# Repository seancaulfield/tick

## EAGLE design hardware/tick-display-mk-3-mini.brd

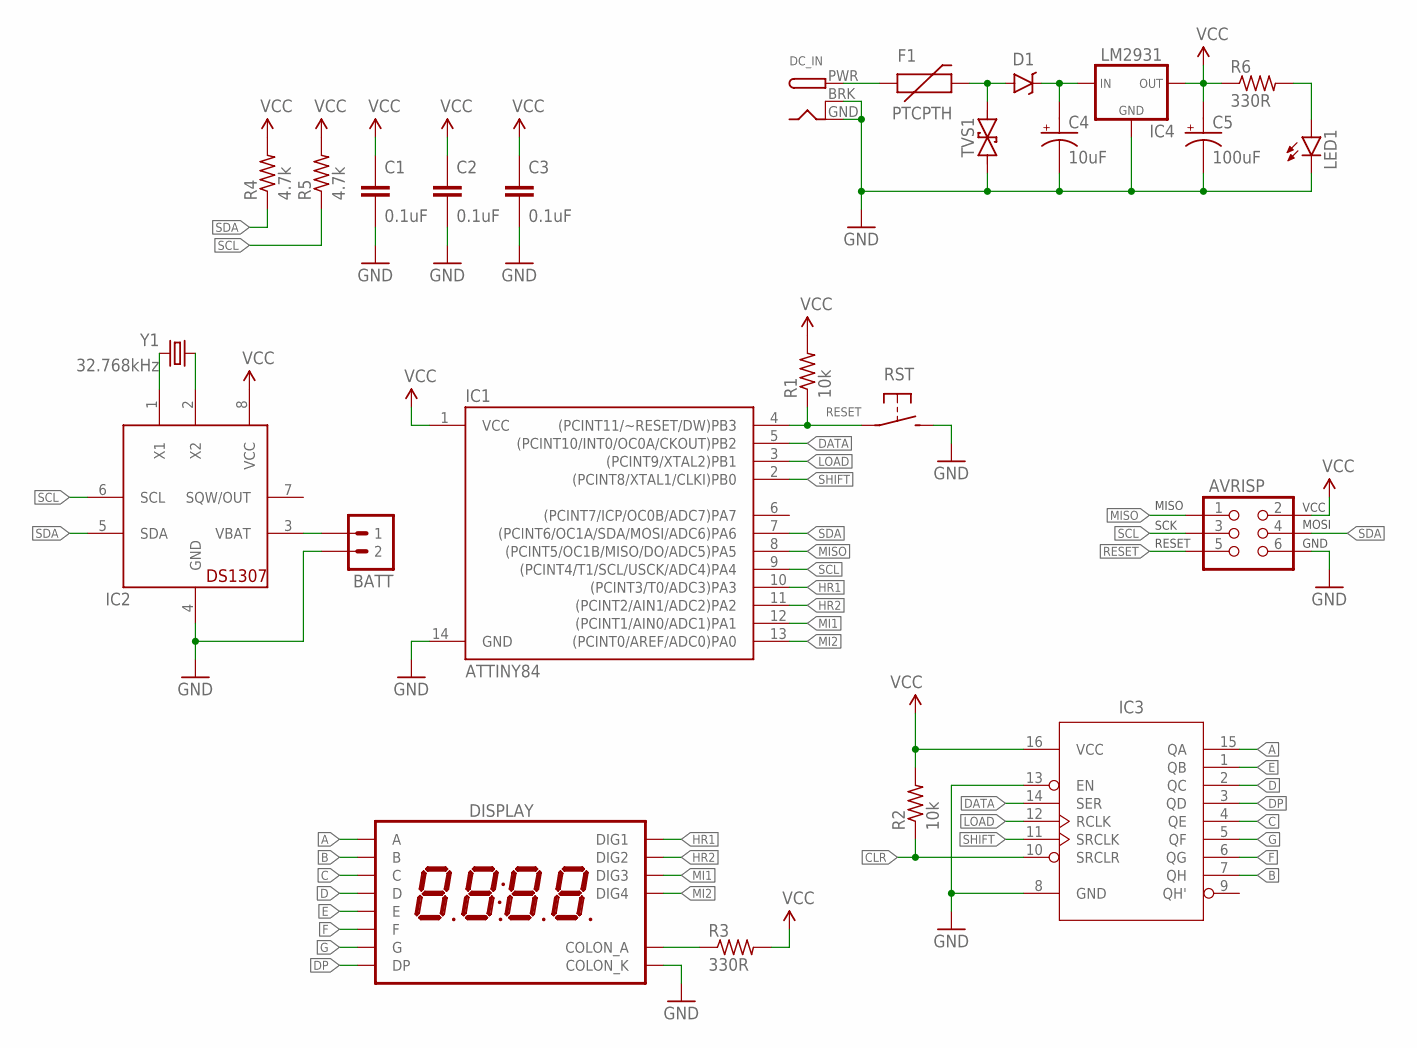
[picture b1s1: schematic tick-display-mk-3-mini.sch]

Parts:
AVRISP: AVR_SPI_PRG_6PTH; 2X3
BATT: M02JST-PTH-VERT; JST-2-PH-VERT-PTH
C1, C2, C3: 0.1uF; C025-024X044
C4: 10uF; E2,5-6
C5: 100uF; E2,5-6
D1: 1N5819; DIODE-7.68MM
DC_IN: DCBARRELPTH; DCJACK_2MM_PTH
DISPLAY: 7SED_4DIGIT_14MM14.2MM-CC-NS; 7SEG_4DIG_NS
F1: PTCPTH; PTC
IC1: ATTINY84; DIL14
IC2: DS1307; DIL08
IC3: 74HCT595; DIL16
IC4: LM2931; TO-92-AMMO
LED1: LED3MM
R1, R2: 10k; RESISTOR-AXIAL-PTH-5.08MM
R3, R6: 330R; RESISTOR-AXIAL-PTH-5.08MM
R4, R5: 4.7k; RESISTOR-AXIAL-PTH-5.08MM
RST: SPST-NO-TACT3MM-RA; TACTILE-PTH-SIDE
TVS1: TVSDO-41-TVS-BIDIRECTIONAL; DO-41-TVS
Y1: 32.768kHz; TC26H

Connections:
A: DISPLAY.P$13 (A), IC3.15 (QA)
B: DISPLAY.P$9 (B), IC3.7 (QH)
C: DISPLAY.P$4 (C), IC3.4 (QE)
CLR: IC3.10 (SRCLR), R2.P$1 (1)
D: DISPLAY.P$2 (D), IC3.2 (QC)
DATA: IC1.5 ((PCINT10/INT0/OC0A/CKOUT)PB2), IC3.14 (SER)
DP: DISPLAY.P$3 (DP), IC3.3 (QD)
E: DISPLAY.P$1 (E), IC3.1 (QB)
F: DISPLAY.P$12 (F), IC3.6 (QG)
G: DISPLAY.P$5 (G), IC3.5 (QF)
GND: AVRISP.6 (GND), BATT.2, C1.2, C2.2, C3.2, C4.-, C5.-, DC_IN.BRK, DC_IN.GND, DISPLAY.P$7 (COLON_K), IC1.14 (GND), IC2.4 (GND), IC3.8 (GND), IC3.13 (EN), IC4.2 (GND), LED1.K (C), RST.2, TVS1.P$1 (1)
HR1: DISPLAY.P$14 (DIG1), IC1.10 ((PCINT3/T0/ADC3)PA3)
HR2: DISPLAY.P$11 (DIG2), IC1.11 ((PCINT2/AIN1/ADC2)PA2)
LOAD: IC1.3 ((PCINT9/XTAL2)PB1), IC3.12 (RCLK)
MI1: DISPLAY.P$10 (DIG3), IC1.12 ((PCINT1/AIN0/ADC1)PA1)
MI2: DISPLAY.P$6 (DIG4), IC1.13 ((PCINT0/AREF/ADC0)PA0)
MISO: AVRISP.1 (MISO), IC1.8 ((PCINT5/OC1B/MISO/DO/ADC5)PA5)
unnamed: BATT.1, IC2.3 (VBAT)
unnamed: DC_IN.PWR, F1.P$1 (1)
unnamed: D1.A, F1.P$2 (2), TVS1.P$2 (2)
unnamed: C4.+, D1.K (C), IC4.1 (IN)
unnamed: IC2.1 (X1), Y1.2
unnamed: IC2.2 (X2), Y1.1
unnamed: LED1.A, R6.P$2 (2)
unnamed: DISPLAY.P$8 (COLON_A), R3.P$1 (1)
RESET: AVRISP.5 (RESET), IC1.4 ((PCINT11/~RESET/DW)PB3), R1.P$1 (1), RST.1
SCL: AVRISP.3 (SCK), IC1.9 ((PCINT4/T1/SCL/USCK/ADC4)PA4), IC2.6 (SCL), R5.P$1 (1)
SDA: AVRISP.4 (MOSI), IC1.7 ((PCINT6/OC1A/SDA/MOSI/ADC6)PA6), IC2.5 (SDA), R4.P$1 (1)
SHIFT: IC1.2 ((PCINT8/XTAL1/CLKI)PB0), IC3.11 (SRCLK)
VCC: AVRISP.2 (VCC), C1.1, C2.1, C3.1, C5.+, IC1.1 (VCC), IC2.8 (VCC), IC3.16 (VCC), IC4.3 (OUT), R1.P$2 (2), R2.P$2 (2), R3.P$2 (2), R4.P$2 (2), R5.P$2 (2), R6.P$1 (1)

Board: 2 copper layers, 25 parts (18 on the bottom side), 30 nets, no tracks yet.

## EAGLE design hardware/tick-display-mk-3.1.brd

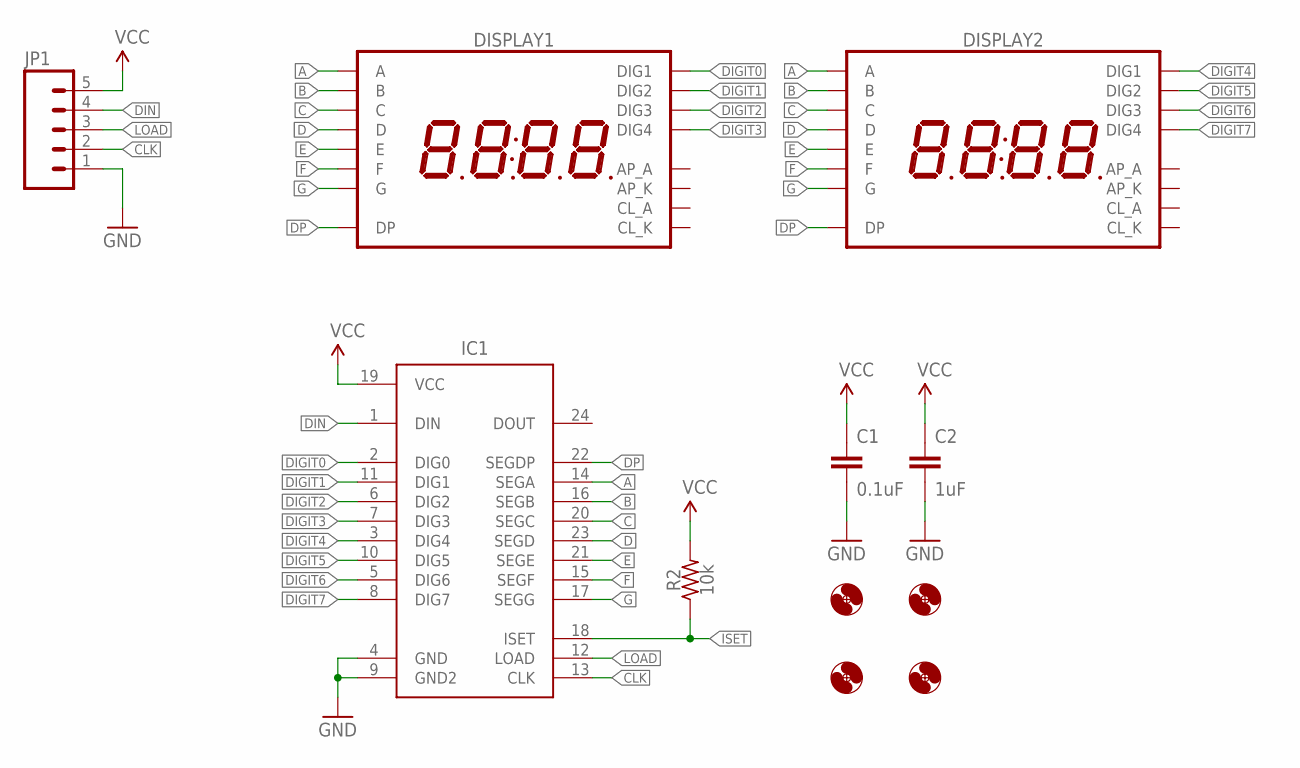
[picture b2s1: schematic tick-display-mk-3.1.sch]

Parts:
C1: 0.1uF; C025-024X044
C2: 1uF; C025-024X044
DISPLAY1, DISPLAY2: 7SEG_4DIGIT_10MM; 7SEG_4DIG_10MM
H1, H2, H3, H4: HOLE#2; HOLE-#2
IC1: MAX7219CWG; SO24W
JP1: M05PTH; 1X05
R2: 10k; RESISTOR-AXIAL-PTH-5.08MM

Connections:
A: DISPLAY1.14 (A), DISPLAY2.14 (A), IC1.14 (SEGA)
B: DISPLAY1.16 (B), DISPLAY2.16 (B), IC1.16 (SEGB)
C: DISPLAY1.13 (C), DISPLAY2.13 (C), IC1.20 (SEGC)
CLK: IC1.13 (CLK), JP1.2
D: DISPLAY1.3 (D), DISPLAY2.3 (D), IC1.23 (SEGD)
DIGIT0: DISPLAY1.1 (DIG1), IC1.2 (DIG0)
DIGIT1: DISPLAY1.2 (DIG2), IC1.11 (DIG1)
DIGIT2: DISPLAY1.6 (DIG3), IC1.6 (DIG2)
DIGIT3: DISPLAY1.8 (DIG4), IC1.7 (DIG3)
DIGIT4: DISPLAY2.1 (DIG1), IC1.3 (DIG4)
DIGIT5: DISPLAY2.2 (DIG2), IC1.10 (DIG5)
DIGIT6: DISPLAY2.6 (DIG3), IC1.5 (DIG6)
DIGIT7: DISPLAY2.8 (DIG4), IC1.8 (DIG7)
DIN: IC1.1 (DIN), JP1.4
DP: DISPLAY1.7 (DP), DISPLAY2.7 (DP), IC1.22 (SEGDP)
E: DISPLAY1.5 (E), DISPLAY2.5 (E), IC1.21 (SEGE)
F: DISPLAY1.11 (F), DISPLAY2.11 (F), IC1.15 (SEGF)
G: DISPLAY1.15 (G), DISPLAY2.15 (G), IC1.17 (SEGG)
GND: C1.2, C2.2, IC1.4 (GND), IC1.9 (GND2), JP1.1
ISET: IC1.18 (ISET), R2.P$1 (1)
LOAD: IC1.12 (LOAD), JP1.3
VCC: C1.1, C2.1, IC1.19 (VCC), JP1.5, R2.P$2 (2)

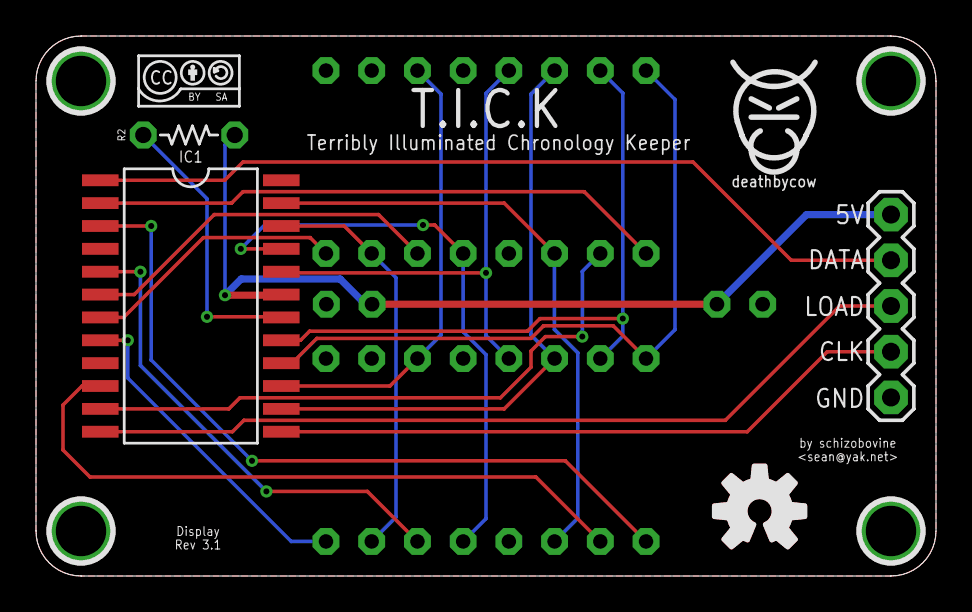
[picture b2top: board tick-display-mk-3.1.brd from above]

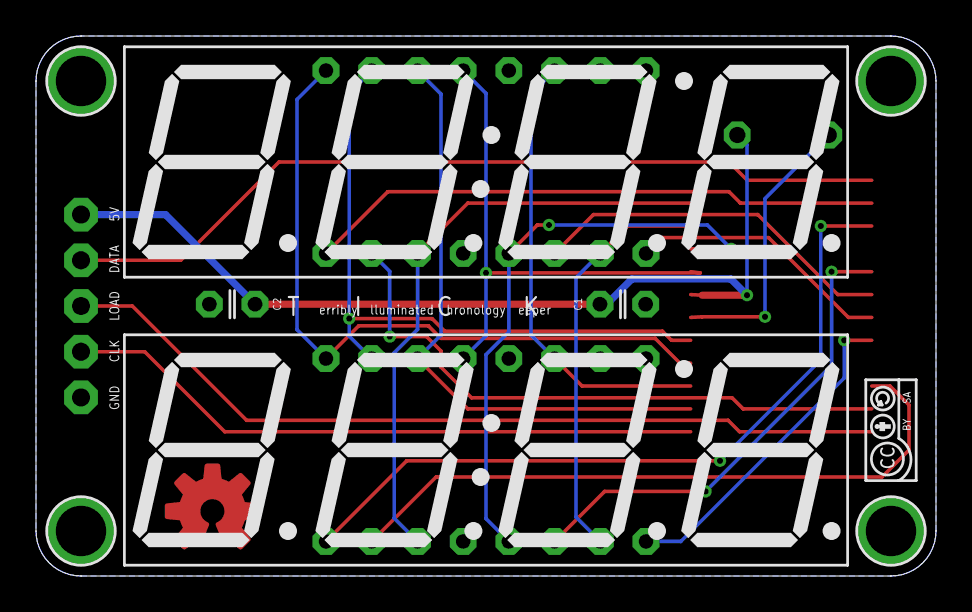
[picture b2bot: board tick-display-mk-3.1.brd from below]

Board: 2 copper layers, 50.0 x 30.0 mm, 15 parts (5 on the bottom side), 22 nets.

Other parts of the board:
U$1: COW_SMALL
U$2, U$3: CC-BY-SA-4.0-NO-URL
U$4: OSHWLOGO_TOP_0.2_A

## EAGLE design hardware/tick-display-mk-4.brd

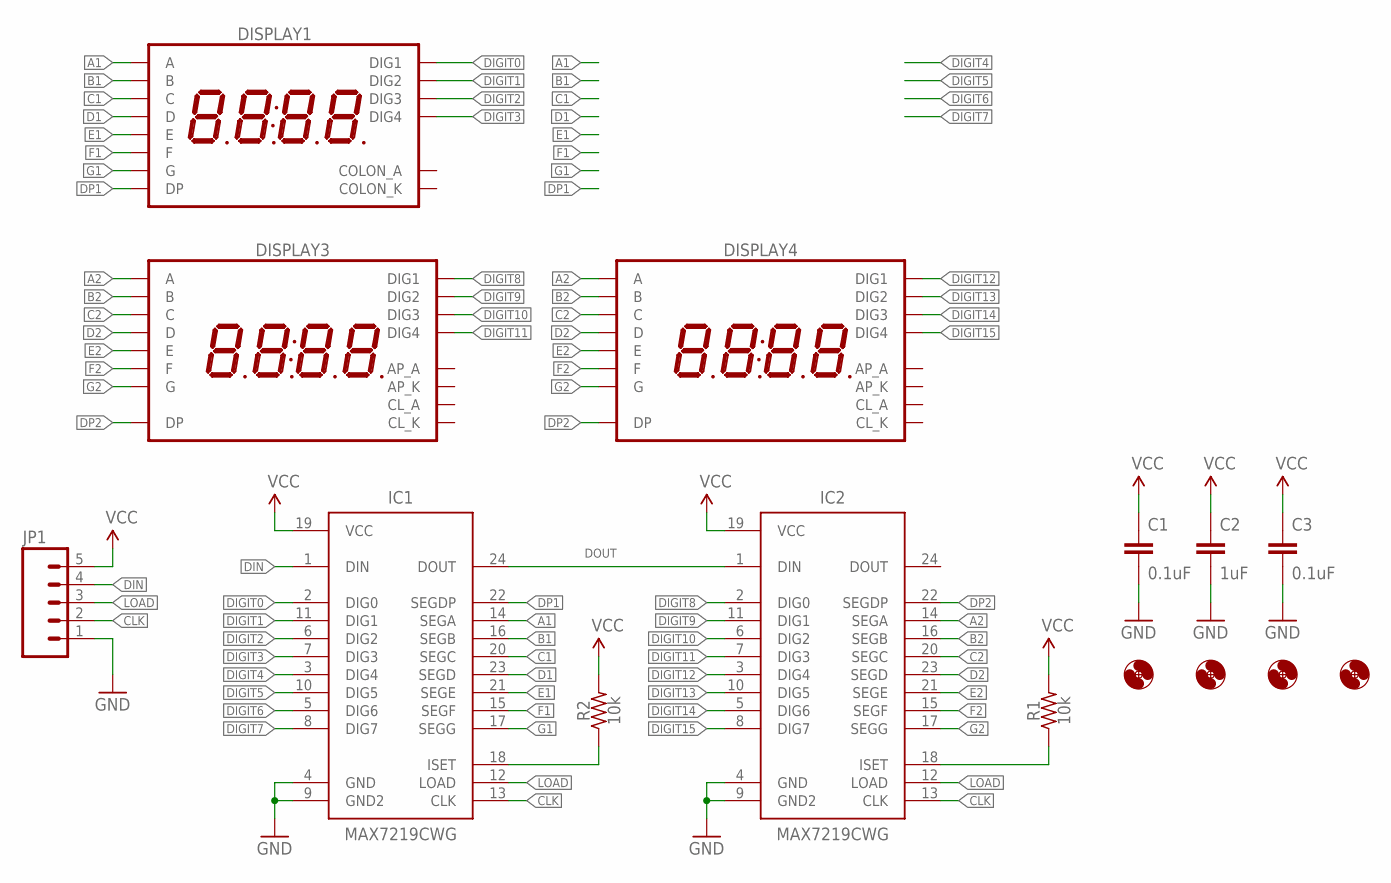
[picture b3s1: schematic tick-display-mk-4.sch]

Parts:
C1, C3: 0.1uF; C025-024X044
C2: 1uF; C025-024X044
DISPLAY1: 7SEG_4DIGIT_COLON14.2MM-CC; 7SEG_4DIG_0.56IN_14MM_ADAFRUIT
DISPLAY3, DISPLAY4: 7SEG_4DIGIT_COLON_APOS; 7SEG_4DIG_10MM
H1, H2, H3, H4: HOLE#2; HOLE-#2
IC1, IC2: MAX7219CWG; SO24W
JP1: M05JST-PH-VERT-PTH; JST-5-PH-VERT-PTH
R1, R2: 10k; RESISTOR-AXIAL-PTH-5.08MM

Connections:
A1: DISPLAY1.P$13 (A), IC1.14 (SEGA)
A2: DISPLAY3.14 (A), DISPLAY4.14 (A), IC2.14 (SEGA)
B1: DISPLAY1.P$9 (B), IC1.16 (SEGB)
B2: DISPLAY3.16 (B), DISPLAY4.16 (B), IC2.16 (SEGB)
C1: DISPLAY1.P$4 (C), IC1.20 (SEGC)
C2: DISPLAY3.13 (C), DISPLAY4.13 (C), IC2.20 (SEGC)
CLK: IC1.13 (CLK), IC2.13 (CLK), JP1.2
D1: DISPLAY1.P$2 (D), IC1.23 (SEGD)
D2: DISPLAY3.3 (D), DISPLAY4.3 (D), IC2.23 (SEGD)
DIGIT0: DISPLAY1.P$14 (DIG1), IC1.2 (DIG0)
DIGIT1: DISPLAY1.P$11 (DIG2), IC1.11 (DIG1)
DIGIT2: DISPLAY1.P$10 (DIG3), IC1.6 (DIG2)
DIGIT3: DISPLAY1.P$6 (DIG4), IC1.7 (DIG3)
DIGIT4: IC1.3 (DIG4)
DIGIT5: IC1.10 (DIG5)
DIGIT6: IC1.5 (DIG6)
DIGIT7: IC1.8 (DIG7)
DIGIT8: DISPLAY3.1 (DIG1), IC2.2 (DIG0)
DIGIT9: DISPLAY3.2 (DIG2), IC2.11 (DIG1)
DIGIT10: DISPLAY3.6 (DIG3), IC2.6 (DIG2)
DIGIT11: DISPLAY3.8 (DIG4), IC2.7 (DIG3)
DIGIT12: DISPLAY4.1 (DIG1), IC2.3 (DIG4)
DIGIT13: DISPLAY4.2 (DIG2), IC2.10 (DIG5)
DIGIT14: DISPLAY4.6 (DIG3), IC2.5 (DIG6)
DIGIT15: DISPLAY4.8 (DIG4), IC2.8 (DIG7)
DIN: IC1.1 (DIN), JP1.4
DOUT: IC1.24 (DOUT), IC2.1 (DIN)
DP1: DISPLAY1.P$3 (DP), IC1.22 (SEGDP)
DP2: DISPLAY3.7 (DP), DISPLAY4.7 (DP), IC2.22 (SEGDP)
E1: DISPLAY1.P$1 (E), IC1.21 (SEGE)
E2: DISPLAY3.5 (E), DISPLAY4.5 (E), IC2.21 (SEGE)
F1: DISPLAY1.P$12 (F), IC1.15 (SEGF)
F2: DISPLAY3.11 (F), DISPLAY4.11 (F), IC2.15 (SEGF)
G1: DISPLAY1.P$5 (G), IC1.17 (SEGG)
G2: DISPLAY3.15 (G), DISPLAY4.15 (G), IC2.17 (SEGG)
GND: C1.2, C2.2, C3.2, IC1.4 (GND), IC1.9 (GND2), IC2.4 (GND), IC2.9 (GND2), JP1.1
LOAD: IC1.12 (LOAD), IC2.12 (LOAD), JP1.3
unnamed: IC1.18 (ISET), R2.P$1 (1)
unnamed: IC2.18 (ISET), R1.P$1 (1)
VCC: C1.1, C2.1, C3.1, IC1.19 (VCC), IC2.19 (VCC), JP1.5, R1.P$2 (2), R2.P$2 (2)

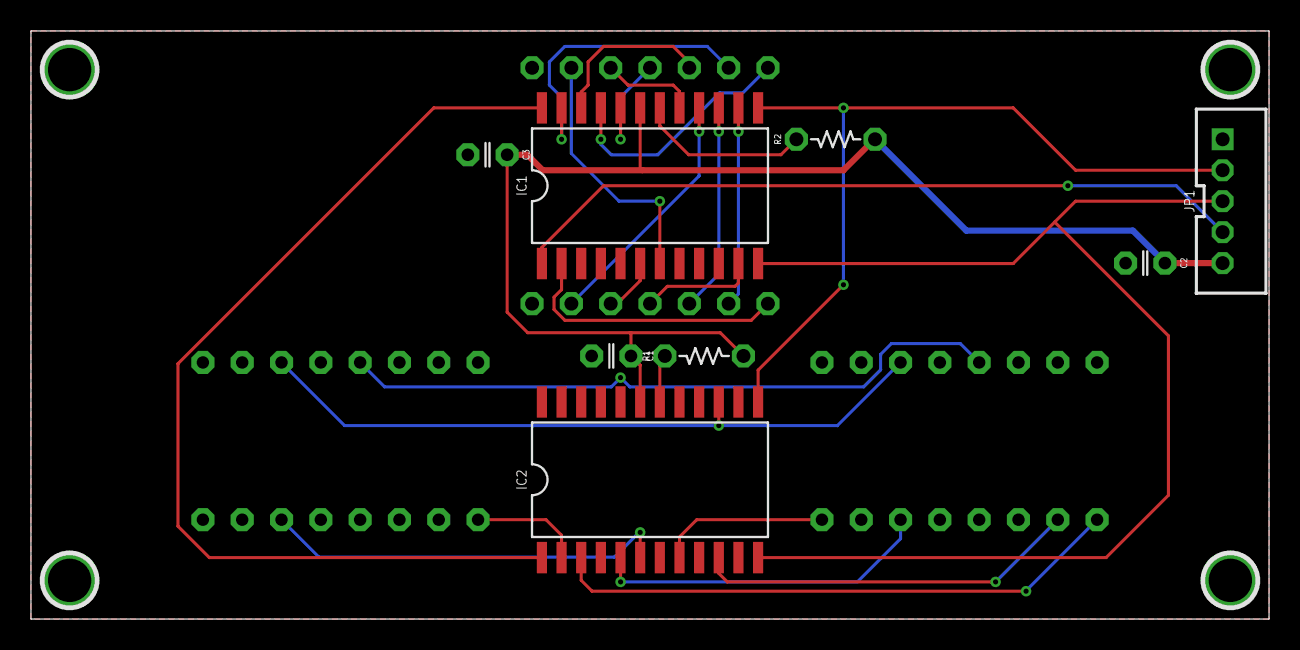
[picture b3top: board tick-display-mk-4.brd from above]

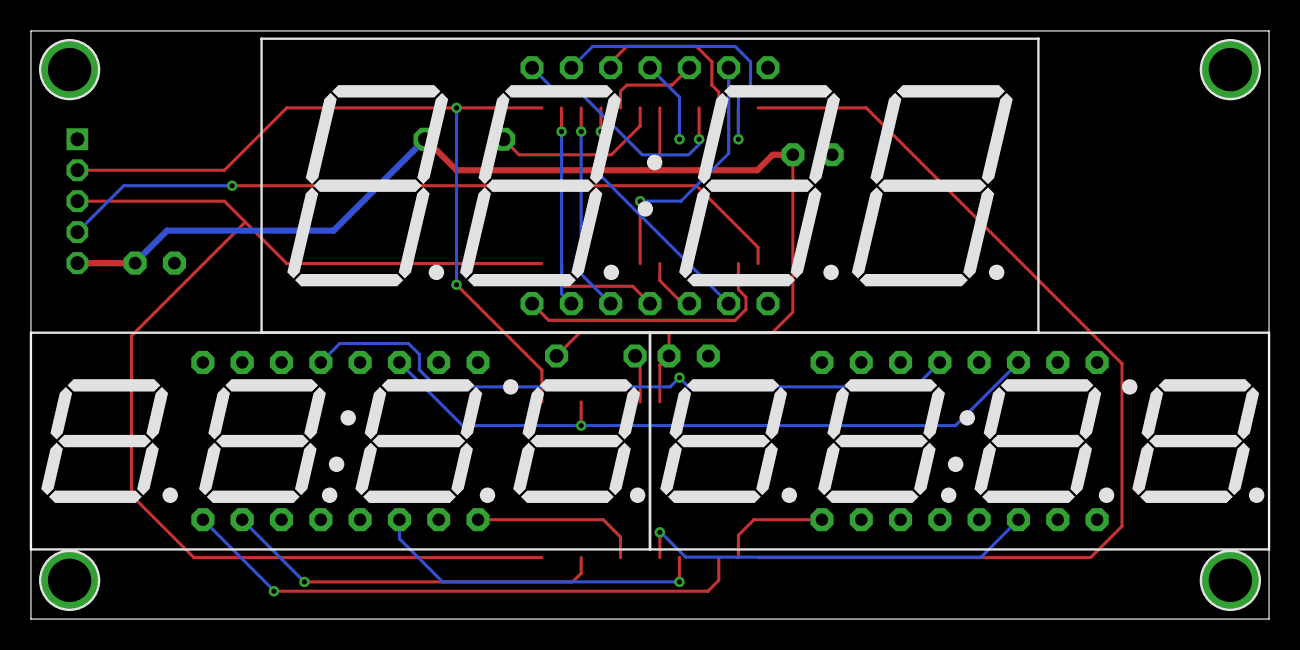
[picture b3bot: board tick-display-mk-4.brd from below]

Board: 2 copper layers, 80.0 x 38.0 mm, 15 parts (3 on the bottom side), 36 nets.

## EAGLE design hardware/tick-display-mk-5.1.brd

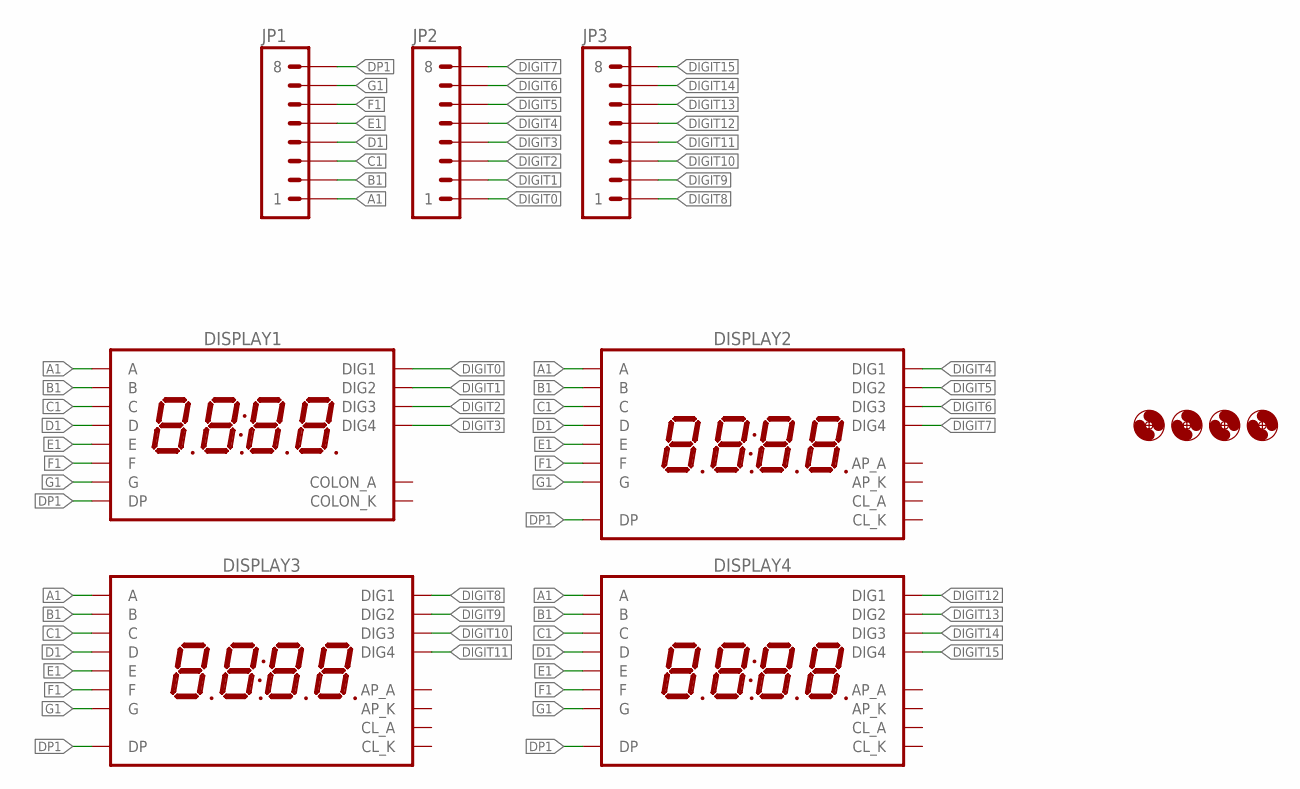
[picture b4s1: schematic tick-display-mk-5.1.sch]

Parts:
DISPLAY1: 7SEG_4DIGIT_COLON14.2MM-CC; 7SEG_4DIG_0.56IN_14MM_ADAFRUIT
DISPLAY2, DISPLAY3, DISPLAY4: 7SEG_4DIGIT_COLON_APOS; 7SEG_4DIG_10MM
H1, H2, H3, H4: HOLE#2; HOLE-#2
JP1, JP2, JP3: M081X08; 1X08

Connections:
A1: DISPLAY1.P$13 (A), DISPLAY2.14 (A), DISPLAY3.14 (A), DISPLAY4.14 (A), JP1.1
B1: DISPLAY1.P$9 (B), DISPLAY2.16 (B), DISPLAY3.16 (B), DISPLAY4.16 (B), JP1.2
C1: DISPLAY1.P$4 (C), DISPLAY2.13 (C), DISPLAY3.13 (C), DISPLAY4.13 (C), JP1.3
D1: DISPLAY1.P$2 (D), DISPLAY2.3 (D), DISPLAY3.3 (D), DISPLAY4.3 (D), JP1.4
DIGIT0: DISPLAY1.P$14 (DIG1), JP2.1
DIGIT1: DISPLAY1.P$11 (DIG2), JP2.2
DIGIT2: DISPLAY1.P$10 (DIG3), JP2.3
DIGIT3: DISPLAY1.P$6 (DIG4), JP2.4
DIGIT4: DISPLAY2.1 (DIG1), JP2.5
DIGIT5: DISPLAY2.2 (DIG2), JP2.6
DIGIT6: DISPLAY2.6 (DIG3), JP2.7
DIGIT7: DISPLAY2.8 (DIG4), JP2.8
DIGIT8: DISPLAY3.1 (DIG1), JP3.1
DIGIT9: DISPLAY3.2 (DIG2), JP3.2
DIGIT10: DISPLAY3.6 (DIG3), JP3.3
DIGIT11: DISPLAY3.8 (DIG4), JP3.4
DIGIT12: DISPLAY4.1 (DIG1), JP3.5
DIGIT13: DISPLAY4.2 (DIG2), JP3.6
DIGIT14: DISPLAY4.6 (DIG3), JP3.7
DIGIT15: DISPLAY4.8 (DIG4), JP3.8
DP1: DISPLAY1.P$3 (DP), DISPLAY2.7 (DP), DISPLAY3.7 (DP), DISPLAY4.7 (DP), JP1.8
E1: DISPLAY1.P$1 (E), DISPLAY2.5 (E), DISPLAY3.5 (E), DISPLAY4.5 (E), JP1.5
F1: DISPLAY1.P$12 (F), DISPLAY2.11 (F), DISPLAY3.11 (F), DISPLAY4.11 (F), JP1.6
G1: DISPLAY1.P$5 (G), DISPLAY2.15 (G), DISPLAY3.15 (G), DISPLAY4.15 (G), JP1.7

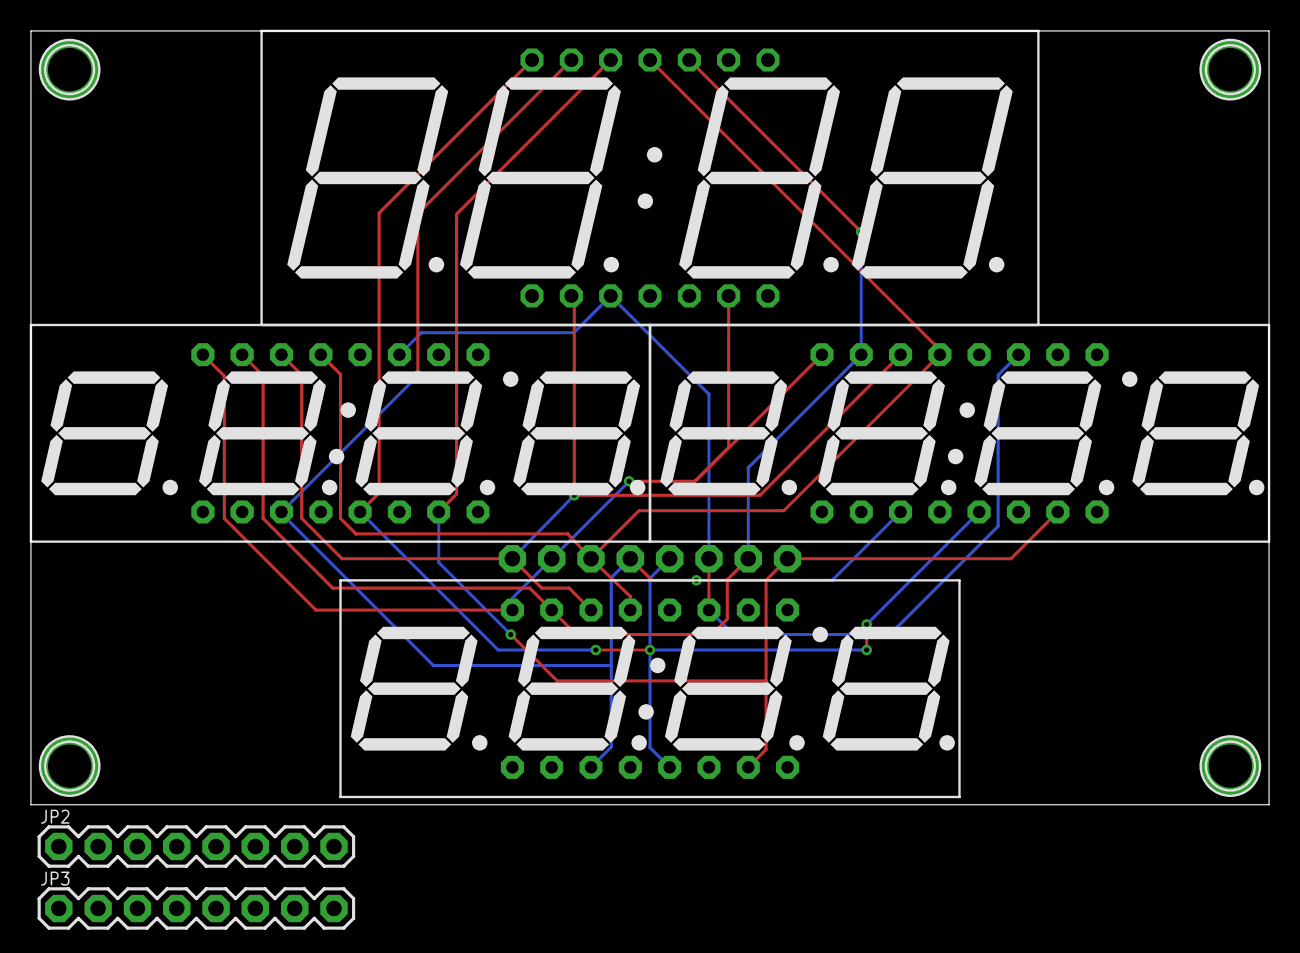
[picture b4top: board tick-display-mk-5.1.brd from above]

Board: 2 copper layers, 80.0 x 50.0 mm, 11 parts (1 on the bottom side), 24 nets.

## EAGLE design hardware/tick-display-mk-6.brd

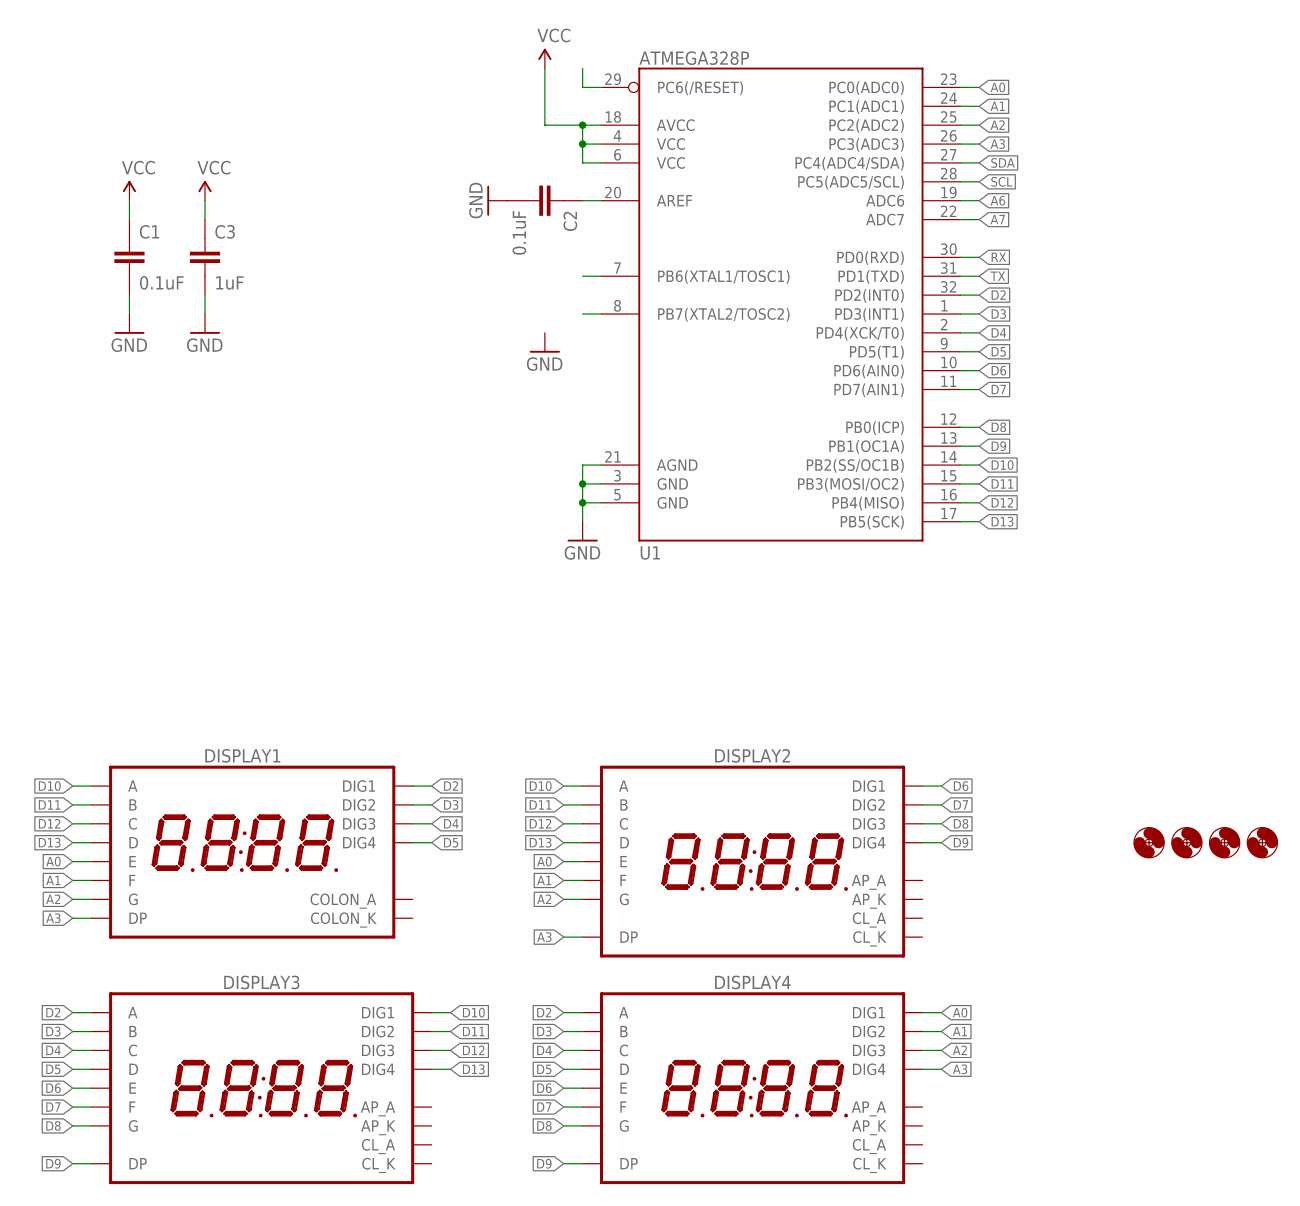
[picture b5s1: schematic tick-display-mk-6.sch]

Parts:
C1, C2: 0.1uF; C0603
C3: 1uF; C0805
DISPLAY1: 7SEG_4DIGIT_COLON14.2MM-CC; 7SEG_4DIG_0.56IN_14MM_ADAFRUIT
DISPLAY2, DISPLAY3, DISPLAY4: 7SEG_4DIGIT_COLON_APOS; 7SEG_4DIG_10MM
H1, H2, H3, H4: HOLE#2; HOLE-#2
U1: ATMEGA328P; TQFP32-08

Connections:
A0: DISPLAY1.P$1 (E), DISPLAY2.5 (E), DISPLAY4.1 (DIG1), U1.23 (PC0(ADC0))
A1: DISPLAY1.P$12 (F), DISPLAY2.11 (F), DISPLAY4.2 (DIG2), U1.24 (PC1(ADC1))
A2: DISPLAY1.P$5 (G), DISPLAY2.15 (G), DISPLAY4.6 (DIG3), U1.25 (PC2(ADC2))
A3: DISPLAY1.P$3 (DP), DISPLAY2.7 (DP), DISPLAY4.8 (DIG4), U1.26 (PC3(ADC3))
A6: U1.19 (ADC6)
A7: U1.22 (ADC7)
D2: DISPLAY1.P$14 (DIG1), DISPLAY3.14 (A), DISPLAY4.14 (A), U1.32 (PD2(INT0))
D3: DISPLAY1.P$11 (DIG2), DISPLAY3.16 (B), DISPLAY4.16 (B), U1.1 (PD3(INT1))
D4: DISPLAY1.P$10 (DIG3), DISPLAY3.13 (C), DISPLAY4.13 (C), U1.2 (PD4(XCK/T0))
D5: DISPLAY1.P$6 (DIG4), DISPLAY3.3 (D), DISPLAY4.3 (D), U1.9 (PD5(T1))
D6: DISPLAY2.1 (DIG1), DISPLAY3.5 (E), DISPLAY4.5 (E), U1.10 (PD6(AIN0))
D7: DISPLAY2.2 (DIG2), DISPLAY3.11 (F), DISPLAY4.11 (F), U1.11 (PD7(AIN1))
D8: DISPLAY2.6 (DIG3), DISPLAY3.15 (G), DISPLAY4.15 (G), U1.12 (PB0(ICP))
D9: DISPLAY2.8 (DIG4), DISPLAY3.7 (DP), DISPLAY4.7 (DP), U1.13 (PB1(OC1A))
D10: DISPLAY1.P$13 (A), DISPLAY2.14 (A), DISPLAY3.1 (DIG1), U1.14 (PB2(SS/OC1B))
D11: DISPLAY1.P$9 (B), DISPLAY2.16 (B), DISPLAY3.2 (DIG2), U1.15 (PB3(MOSI/OC2))
D12: DISPLAY1.P$4 (C), DISPLAY2.13 (C), DISPLAY3.6 (DIG3), U1.16 (PB4(MISO))
D13: DISPLAY1.P$2 (D), DISPLAY2.3 (D), DISPLAY3.8 (DIG4), U1.17 (PB5(SCK))
GND: C1.2, C2.2, C3.2, U1.3 (GND), U1.5 (GND), U1.21 (AGND)
unnamed: C2.1, U1.20 (AREF)
RX: U1.30 (PD0(RXD))
SCL: U1.28 (PC5(ADC5/SCL))
SDA: U1.27 (PC4(ADC4/SDA))
TX: U1.31 (PD1(TXD))
VCC: C1.1, C3.1, U1.4 (VCC), U1.6 (VCC), U1.18 (AVCC)

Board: 2 copper layers, 12 parts (3 on the bottom side), 19 nets, no tracks yet.
